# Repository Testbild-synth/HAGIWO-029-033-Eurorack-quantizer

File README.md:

# HAGIWO 029/033 Eurorack Quantizer Module

Through hole PCB version of the [HAGIWO 033 dual quantizer](https://www.youtube.com/watch?v=6FJpljEYZq4) and [029 SH101 sequencer](https://www.youtube.com/watch?v=--qb_QYZrTk) Eurorack Module. The modules uses a seeduino xiao and a mcp4725 dac.

The dual quantizer quantizes to notes selectable on the screen and can automatically trigger an envelope on note changes.
The SH101 sequencer allows recording and playback of cv sequences.

## Status
kind of abandoned, this is an old project and I never got around to smoothing out the kinks. Will do a new version sometimes soontm.
I cannot recommend building it at the moment.

## Hardware and PCB

You can find the schematic and BOM in the root folder.
For the PCBs, the module has one main circuit PCB, one control circuit PCB and one panel PCB. 
You can order them on any common PCB manufacturing service, I used [JLCPCB](https://jlcpcb.com/).
I made the circuits pcbs under 100mm to get the discount price.
Standard settings should be fine, but as there is exposed copper on the panel you should go with a lead free surface finish (ENIG/Leadfree HASL).
If the panel size is not correctly detected by JLC (happens on some of my exports) manually put 30x128.5 mm.

when ordering the display module, make sure to choose an 0.96 I2C oled module that has the pinout specified as GND-VCC-SCL-SDA as opposed to VCC-GND-SCL-SDA (both exist and the latter will fuck it up).    

Also make sure you order a Seediuno XIAO (with a SAMD21/Cortex M0 chip) as opposed to the XIAO esp32c3 or the XIAO rp2040, those are different chips.

## Assembly

When assembling, you can either use a header for the screen or solder it directly, as it is a litte too tall.
The 7805 voltage regulator is optional, if you do not want to use it, simply solder the SEL header on the back of the main pcb to BOARD instead of REG (meaning you bridge the connection to choose your 5v voltage source to either be 12 regulated to 5v, or a 5V connection of your rack power if you have it).

## Tuning
There are two things  in the circuit that need to be tuned for: The input resistor divider going from 5V to 3.3V, and the output opamp gain to go from 3.3 back to 5V.
I will provide a script to help with this and a detailed description in the future, but for now the short version is: Input resistors are compensated for in code with the ADC_calb parameters. Output gain is adjusted using the trimmers on the main pcb.

## Arduino Code

### Double Quantizer
HAGIWO did great work, but I decided to make some changes to the Arduino code because I had ADC issues on my seeduino Xiao.

The main changes are:
 - HAGIWO had a check that cv is only updated then there's a big enough change from the last value. I took this out since I want to be able to process slow cv changes (i.e. from LFOs), also. 
 - I followed suggestions from [this very nice blog about adc accuracy on samd21](https://blog.thea.codes/getting-the-most-out-of-the-samd21-adc/). With lower input impedance and the changes from this blog, the readings got a lot more accurate on mine. Downside is more latency (in the single ms range) but frankly im willing to take that for more stability/less noise.
 - Also, to make use of this, the note calculation is now done with 12 bit instead of downsampling the adc values to 10 bit.
 - Comment out the specified lines in the code if you dont want the slower adc.

## TODO:
- Test and verify SH101 firmware
- maybe add display indication for played notes

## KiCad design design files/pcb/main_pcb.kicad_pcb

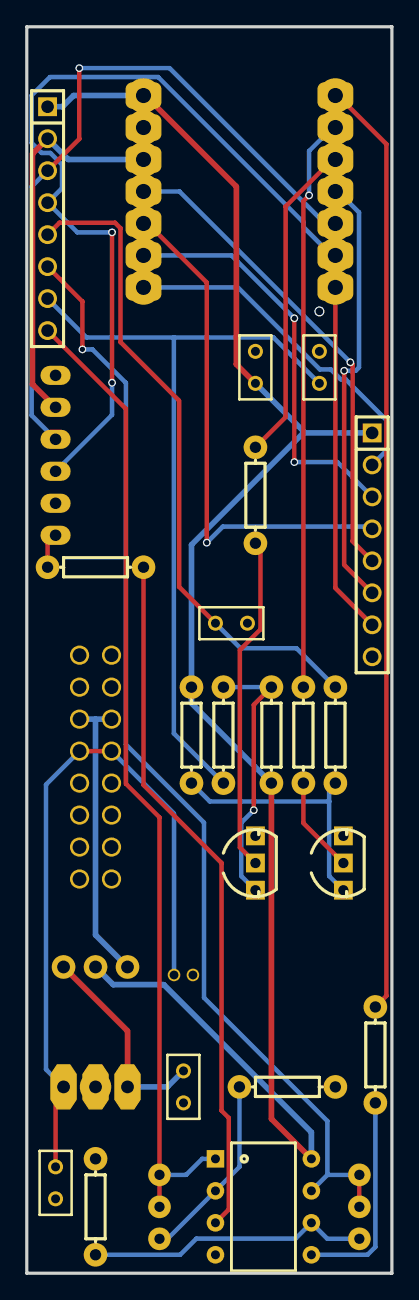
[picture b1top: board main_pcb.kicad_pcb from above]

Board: 2 copper layers, 29.0 x 99.0 mm, 28 parts (0 on the bottom side), 30 nets.

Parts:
C1, C4: 470n; RAD-0.1
C2, C5, C6: 100n; RAD-0.1
C3: 10u; CAP-D4.0×F1.5
CN1: MCP4725-B
H4, H5: Header-Male-2.54_1x8; HDR-TH_8P-P2.54-V-M
P1: PWR; HDR-IDC-2.54-2X8P
Q1, Q2: BC547A; TO92-INLINE
R1, R7: 10k; R_AXIAL-0.3
R2, R8: 6.8k; R_AXIAL-0.3
R3, R9: 5K; TRIMPOT-ELETROCURSOS-FOOTPRINT
R4, R5, R10, R11: 330; R_AXIAL-0.3
R6, R12: 1k; R_AXIAL-0.3
SEEDUINO: Seeeduino XIAO; SEEDUINO XIAO
SEL: M03PTH; 1X03
U1: MCP6002-EP; DIP8
U3: 7805

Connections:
5V: C2.2, H4.1, H5.1, R4.2, R10.2, SEEDUINO.14, SEL.2, U1.8
ARD_3: CN1.5, H5.2, SEEDUINO.12
CN1_1: CN1.1, R1.1
ENC_1: H4.6, SEEDUINO.4
ENC_2: H4.7, SEEDUINO.7
ENC_SW: H4.5, SEEDUINO.11
GND: C1.2, C2.1, C3.2, C4.2, C5.1, C6.2, CN1.2, CN1.6, H4.8, P1.3, P1.4, P1.5, P1.6, P1.7, P1.8, Q1.3, Q2.3, R2.1, R8.1, SEEDUINO.13, U1.4, U3.2
IN_1: H4.2, SEEDUINO.8
IN_2: H4.3, SEEDUINO.9
IN_3: H4.4, SEEDUINO.10
O1: R6.1, SEEDUINO.2
O1_CON: C1.1, H5.5, R5.1
O2: R7.1, SEEDUINO.1
O2_CON: H5.6, R9.2, R9.3, U1.7
O3: R12.1, SEEDUINO.3
O3_CON: C4.1, H5.7, R11.1
O4_CON: H5.8, R3.2, R3.3, U1.1
P1_10: C3.1, C5.2, P1.9, P1.10, U3.1
POW_5: P1.11, P1.12, SEL.3
Q1_1: Q1.1, R4.1, R5.2
Q2_1: Q2.1, R10.1, R11.2
R1_2: R1.2, U1.3
R2_2: R2.2, R3.1, U1.2
R6_2: Q1.2, R6.2
R7_2: R7.2, U1.5
R9_1: R8.2, R9.1, U1.6
R12_2: Q2.2, R12.2
REG_5: C6.1, SEL.1, U3.3
SCL: CN1.3, H5.4, SEEDUINO.6
SDA: CN1.4, H5.3, SEEDUINO.5

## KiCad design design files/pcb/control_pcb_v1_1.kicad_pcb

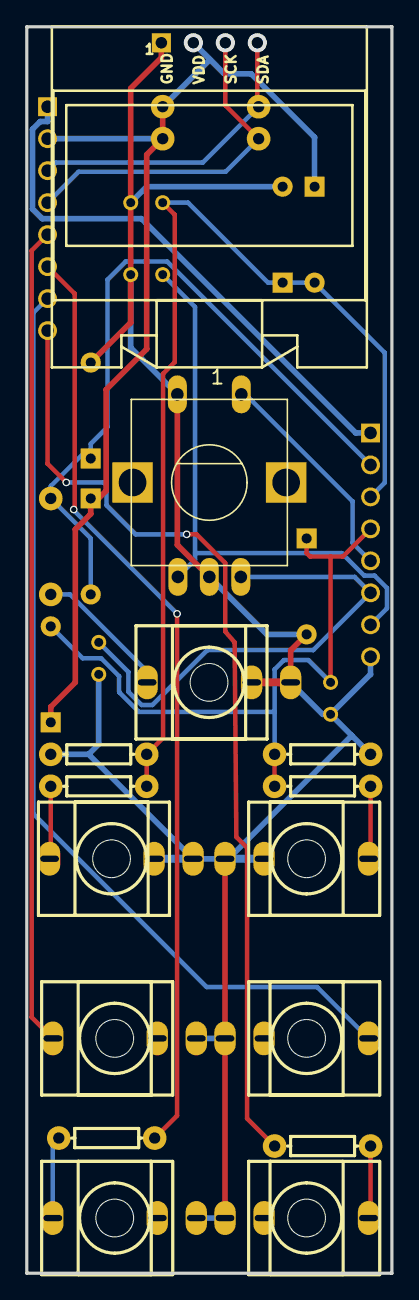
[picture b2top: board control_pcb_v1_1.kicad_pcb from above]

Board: 2 copper layers, 29.0 x 99.0 mm, 29 parts (0 on the bottom side), 20 nets.

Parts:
1: ALPS_ENCODER+PUSHSWITCHNORMAL; ENCODER+SWITCH
C7, C8, C9, C10: 10n; RAD-0.1
D1, D2, D3, D4, D5, D6: BAT43; D_DO-35_SOD27_P7.62MM_HORIZONTAL
H1, H2: Header-Male-2.54_1x8; HDR-TH_8P-P2.54-V-M
J1: O4; THONKICONN_1
J2: IN3; THONKICONN_1
J3: O1; THONKICONN_1
J4: IN1; THONKICONN_1
J5: IN2; THONKICONN_1
J6: O2; THONKICONN_1
J7: O3; THONKICONN_1
R13, R20: 470; R_AXIAL-0.3
R14, R19: 18k; R_AXIAL-0.3
R15, R18, R21: 33k; R_AXIAL-0.3
R16, R17: 3k3; R_AXIAL-0.3

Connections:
5V: H1.1, H2.1
ARD_3: D1.1, D3.1, D4.1, H2.2, R16.1, R17.1
ENC_1: 1.B, C8.2, H1.6
ENC_2: 1.A, C9.1, H1.7
ENC_SW: 1.E, H1.5
GND: 1.C, 1.D, C7.1, C8.1, C9.2, C10.1, D2.2, D5.2, D6.2, H1.8, J1.1, J2.1, J2.2, J3.1, J4.1, J4.2, J5.1, J5.2, J6.1, J7.1, R15.2, R21.2
IN_1: D3.2, D5.1, H1.2, R18.1
IN_2: C10.2, D4.2, D6.1, H1.3, R19.1, R21.1
IN_3: C7.2, D1.2, D2.1, H1.4, R14.1, R15.1
J1_3: J1.3, R13.2
J5_3: J5.3, R19.2
J6_3: J6.3, R20.2
O1_CON: H2.5, J3.3
O2_CON: H2.6, R20.1
O3_CON: H2.7, J7.3
O4_CON: H2.8, R13.1
R14_2: J2.3, R14.2
R18_2: J4.3, R18.2
SCL: H2.4, R17.2
SDA: H2.3, R16.2

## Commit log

2022-02-04 upload new bom and design files for main pcb
2022-02-04 ujploaded images
2022-04-07 firmware quantizer
2022-04-07 moved
2023-03-10 added panel pcb that was missing for whatever reason
2023-03-10 added inkscape file for panel
2023-07-04 fixed orientation for mcp6002
